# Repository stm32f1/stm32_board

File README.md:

# stm32\_microcontroller\_board

## Introduction

General stm32 microcontroller board

---
### Peripheral

* POWER
  - Input Voltage: 6V to 14V

* OUTPUT
  - BUZZER  
  - two debug LED

* INPUT
  - two tactile switch

* COMMUNICATION
  - UART1: 3pin connector(debug)  
  - UART3: 2\*5 connector(wireless communication)  
  - SPI3: 2\*5 connector(SD card and motion sensor)

---
#### License
* This hardware is released under the MIT License, see LICENSE.

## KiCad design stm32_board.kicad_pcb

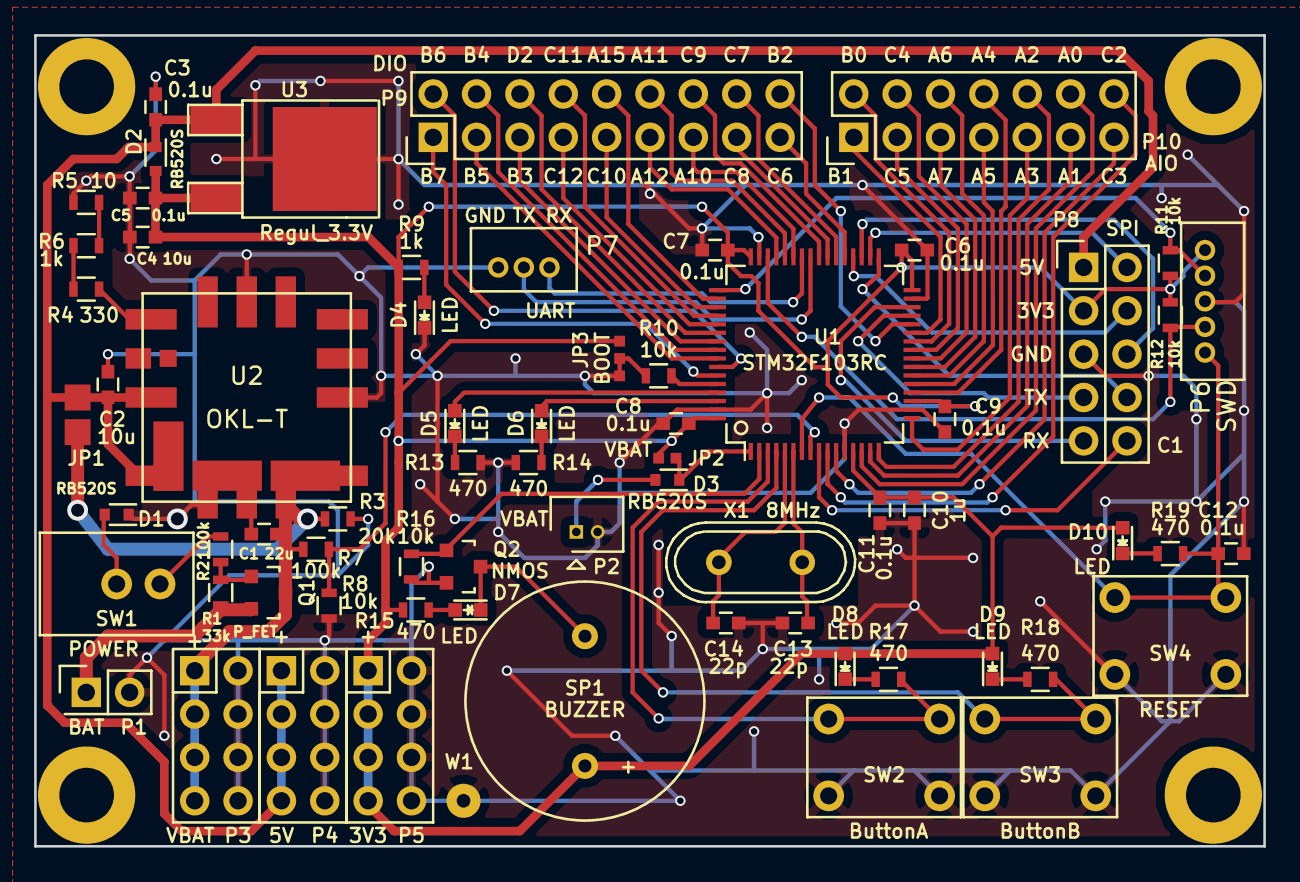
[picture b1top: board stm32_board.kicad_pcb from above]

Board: 2 copper layers, 72.0 x 47.5 mm, 68 parts (0 on the bottom side), 74 nets.

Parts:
C1: 22u; C_0603
C2, C4: 10u; C_0603
C3, C5, C6, C7, C8, C9, C11, C12: 0.1u; C_0603
C10: 1u; C_0603
C13, C14: 22p; C_0603
D1, D2, D3: RB520S; SOD-523
D4, D5, D6, D7, D8, D9, D10: LED; LED_0603
JP1: Vin_select; Jumper
JP2: VBAT; Jumper_S
JP3: BOOT; Jumper_3P
P1: BAT; Pin_Header_Straight_2x01
P2: VBAT; Molex_PicoBlade_53047-0210
P3: VBAT; Power_2x04
P4: 5V; Power_2x04
P5: 3V3; Power_2x04
P6: SWD; ZH-5P
P7: UART; ZH-3P
P8: EXPANSION_CONN; EX_CONN
P9: DIO
P10: AIO
Q1: P_FET; SOT-23
Q2: NMOS; SOT-23
R1: 33k; R_0603
R2, R7: 100k; R_0603
R3: 20k; R_0603
R4, R9: 1k; R_0603
R5: 330; R_0603
R6: 10; R_0603
R8, R10, R11, R12, R16: 10k; R_0603
R13, R14, R15, R17, R18, R19: 470; R_0603
SP1: BUZZER; SPB04
SW1: POWER; MS-611K
SW2: ButtonA; tactile_switch
SW3: ButtonB; tactile_switch
SW4: RESET; tactile_switch
U1: STM32F103RC; LQFP-64
U2: OKL-T; OKL_T6
U3: Regul_3.3V; TO-252-2Lead
W1: TEST_1P; SolderWirePad_single_0-8mmDrill
X1: 8MHz; Crystal_HC49-U_Vertical

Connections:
+5V: C2.1, C3.1, D2.1, JP1.2, P4.1, P4.3, P4.5, P4.7, P8.1, U2.4, U2.5, U3.1
+BATT: D3.1, JP2.2, U1.1
/PA0: P10.12, U1.14
/PA1: P10.11, U1.15
/PA2: P10.10, U1.16
/PA3: P10.9, U1.17
/PA4: P10.8, U1.20
/PA5: P10.7, U1.21
/PA6: P10.6, U1.22
/PA7: P10.5, U1.23
/PA10: P9.13, U1.43
/PA11: P9.12, U1.44
/PA12: P9.11, U1.45
/PA15: P9.10, U1.50
/PB0: P10.2, U1.26
/PB1: P10.1, U1.27
/PB3: P9.5, U1.55
/PB4: P9.4, U1.56
/PB5: P9.3, U1.57
/PB6: P9.2, U1.58
/PB7: P9.1, U1.59
/PC1: P8.10, U1.9
/PC2: P10.14, U1.10
/PC3: P10.13, U1.11
/PC4: P10.4, U1.24
/PC5: P10.3, U1.25
/PC6: P9.17, U1.37
/PC7: P9.16, U1.38
/PC8: P9.15, U1.39
/PC9: P9.14, U1.40
/PC10: P9.9, U1.51
/PC11: P9.8, U1.52
/PC12: P9.7, U1.53
/PD2: P9.6, U1.54
BAT_CHK: R7.2, R8.1, U1.8
BOOT0: R10.2, U1.60
BOOT1: P9.18, U1.28
BUTTON_A: R17.2, SW2.1, SW2.2, U1.3
BUTTON_B: R18.2, SW3.1, SW3.2, U1.4
BUZZER: Q2.1, R16.1, U1.2
GND: C1.2, C2.2, C3.2, C4.2, C5.2, C6.2, C7.2, C8.2, C9.2, C10.2, C11.2, C12.2, C13.1, C14.1, D1.1, D4.1, JP3.1, JP3.2, P1.2, P2.2, P3.2, P3.4, P3.6, P3.8, P4.2, P4.4, P4.6, P4.8, P5.2, P5.4, P5.6, P5.8, P6.3, P7.1, P8.5, Q2.2, R3.2, R6.2, R8.2, R10.1, R13.2, R14.2, R16.2, SW2.3, SW2.4, SW3.3, SW3.4, SW4.3, SW4.4, U1.12, U1.18, U1.31, U1.47, U1.63, U2.1, U2.3, U2.7, U3.2, W1.1
LED_A: D5.2, U1.61
LED_B: D6.2, U1.62
NRST: C12.1, P6.5, R19.2, SW4.1, SW4.2, U1.7
unnamed: C13.2, U1.6, X1.2
unnamed: C14.2, U1.5, X1.1
unnamed: D1.2, SW1.1
unnamed: D3.2, P2.1
unnamed: D4.2, R9.2
unnamed: D5.1, R13.1
unnamed: D6.1, R14.1
unnamed: D7.1, Q2.3, SP1.2
unnamed: D7.2, R15.2
unnamed: D8.1, R17.1
unnamed: D9.1, R18.1
unnamed: D10.1, R19.1
unnamed: P1.1, Q1.2, R1.2
unnamed: Q1.1, R1.1, R2.2
unnamed: R2.1, SW1.2
unnamed: R4.1, U2.6
unnamed: R4.2, R5.1
unnamed: R5.2, R6.1
SPI2_MISO: P8.6, U1.35
SPI2_MOSI: P8.4, U1.36
SPI2_NSS: P8.8, U1.33
SPI2_SCK: P8.2, U1.34
SWCLK: P6.2, R11.2, U1.49
SWDIO: P6.4, R12.2, U1.46
UART3_RX: P8.9, U1.30
UART3_TX: P8.7, U1.29
UART_RX: P7.3, U1.42
UART_TX: P7.2, U1.41
VDD: C4.1, C5.1, C6.1, C7.1, C8.1, C9.1, C10.1, C11.1, D2.2, D8.2, D9.2, D10.2, JP2.1, JP3.3, P5.1, P5.3, P5.5, P5.7, P6.1, P8.3, R9.1, R11.1, R12.1, R15.1, SP1.1, U1.13, U1.19, U1.32, U1.48, U1.64, U3.3
VIN: C1.1, JP1.1, P3.1, P3.3, P3.5, P3.7, Q1.3, R3.1, R7.1, U2.2
